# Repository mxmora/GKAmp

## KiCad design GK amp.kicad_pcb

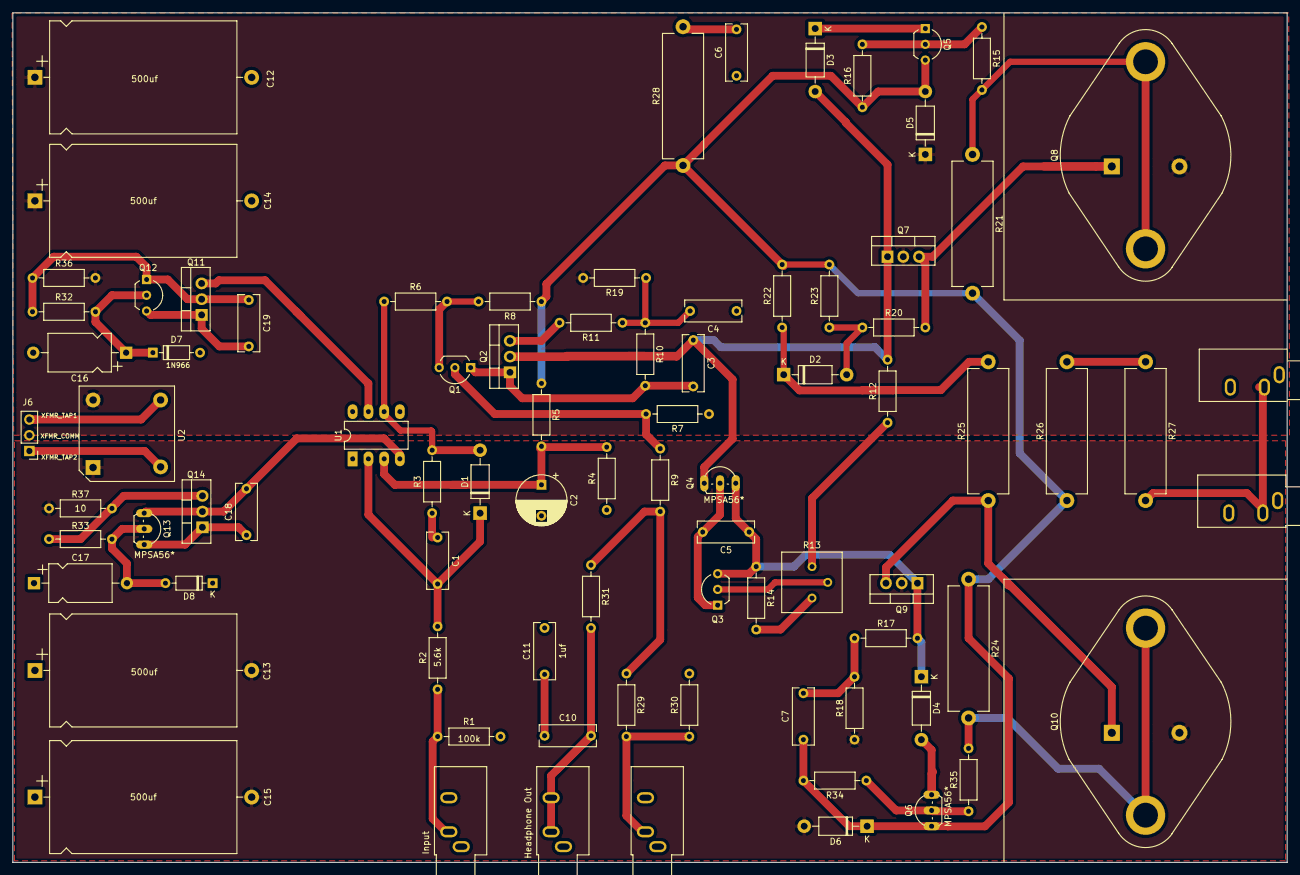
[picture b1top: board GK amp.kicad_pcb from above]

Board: 2 copper layers, 205.7 x 137.2 mm, 84 parts (0 on the bottom side), 48 nets.

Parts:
C1, C6: .1uf; C_Rect_L9.0mm_W3.3mm_P7.50mm_MKT
C2: 10uf; CP_Radial_D8.0mm_P5.00mm
C3: 100pF; C_Rect_L9.0mm_W3.3mm_P7.50mm_MKT
C4: 500; C_Rect_L9.0mm_W3.3mm_P7.50mm_MKT
C5: .01uf; C_Rect_L9.0mm_W3.3mm_P7.50mm_MKT
C7: 220uf; C_Rect_L9.0mm_W3.3mm_P7.50mm_MKT
C10, C11: 1uf; C_Rect_L9.0mm_W3.3mm_P7.50mm_MKT
C12, C13, C14, C15: 500uf; CP_Axial_L30.0mm_D18.0mm_P35.00mm_Horizontal
C16, C17: 10uf; CP_Axial_L10.0mm_D6.0mm_P15.00mm_Horizontal
C18, C19: 500pF; C_Rect_L9.0mm_W3.3mm_P7.50mm_MKT
D1, D2, D3, D4, D5, D6: 1N4002; D_DO-41_SOD81_P10.16mm_Horizontal
D7, D8: Zen; D_DO-35_SOD27_P7.62mm_Horizontal
J1, J2: SPEAKER; Jack_3.5mm_CUI_SJ1-3533NG_Horizontal
J3: Direct Out; Jack_3.5mm_CUI_SJ1-3533NG_Horizontal
J4: AudioJack3; Jack_3.5mm_CUI_SJ1-3533NG_Horizontal
J5: IN; Jack_3.5mm_CUI_SJ1-3533NG_Horizontal
J6: Conn_01x03_Male; PinHeader_1x03_P2.54mm_Vertical
Q1, Q3, Q5, Q12: MPSA06; TO-92_Inline_Wide
Q2, Q9: MJE15031; TO-220-3_Vertical
Q4, Q6, Q13: MPSA56*; TO92-CBE
Q7: MJE15030; TO-220-3_Vertical
Q8: MJ-15001; TO-3
Q10: MJ-15002; TO-3
Q11, Q14: TIP31; TO-220-3_Vertical
R1, R3: 100k; R_Axial_DIN0207_L6.3mm_D2.5mm_P10.16mm_Horizontal
R2: 5.6k; R_Axial_DIN0207_L6.3mm_D2.5mm_P10.16mm_Horizontal
R4, R29: 12k; R_Axial_DIN0207_L6.3mm_D2.5mm_P10.16mm_Horizontal
R5, R32, R33: 56k; R_Axial_DIN0207_L6.3mm_D2.5mm_P10.16mm_Horizontal
R6, R8: 3.74k; R_Axial_DIN0207_L6.3mm_D2.5mm_P10.16mm_Horizontal
R7: 4.75k; R_Axial_DIN0207_L6.3mm_D2.5mm_P10.16mm_Horizontal
R9: 4.99k; R_Axial_DIN0207_L6.3mm_D2.5mm_P10.16mm_Horizontal
R10, R14, R15: 1k; R_Axial_DIN0207_L6.3mm_D2.5mm_P10.16mm_Horizontal
R11: 100; R_Axial_DIN0207_L6.3mm_D2.5mm_P10.16mm_Horizontal
R12: 3.3k; R_Axial_DIN0207_L6.3mm_D2.5mm_P10.16mm_Horizontal
R13: 1k; Potentiometer_Bourns_3386P_Vertical
R16, R22, R23, R30, R34: 470; R_Axial_DIN0207_L6.3mm_D2.5mm_P10.16mm_Horizontal
R17, R18, R31: 2.7k 1W; R_Axial_DIN0207_L6.3mm_D2.5mm_P10.16mm_Horizontal
R19, R20: 22; R_Axial_DIN0207_L6.3mm_D2.5mm_P10.16mm_Horizontal
R21, R24, R26, R27: .33 5W; R_Axial_Power_L20.0mm_W6.4mm_P22.40mm
R25: 22; R_Axial_Power_L20.0mm_W6.4mm_P22.40mm
R28: 5 5w; R_Axial_Power_L20.0mm_W6.4mm_P22.40mm
R35: 1K; R_Axial_DIN0207_L6.3mm_D2.5mm_P10.16mm_Horizontal
R36, R37: 10; R_Axial_DIN0207_L6.3mm_D2.5mm_P10.16mm_Horizontal
U1: LF351N; DIP-8_W7.62mm_LongPads
U2: Bridge; Diode_Bridge_15.1x15.1x6.3mm_P10.9mm

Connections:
A: C12.1, C14.1, D5.1, Q7.2, Q8.2, R19.2, R36.2, U2.4
B: Q11.3, U1.7
C: C18.2, Q13.E, Q14.2, U1.4
D: C13.2, C15.2, D6.2, Q9.2, Q10.2, R18.1, R37.2, U2.1
GND: C2.2, C4.1, C6.1, C11.2, C12.2, C13.1, C14.2, C15.1, C16.2, C17.1, D7.2, D8.1, J1.S, J2.S, J3.S, J4.S, J5.S, J6.2, R1.1, R4.1, R7.1, R30.2
unnamed: C1.1, R3.1
unnamed: C1.2, D1.1, R2.2, U1.2
unnamed: C2.1, R4.2, R5.2, U1.3
unnamed: C3.1, D3.2, Q2.2, Q4.E, Q7.1, R12.2
unnamed: C3.2, Q1.1, Q2.1, R10.2
unnamed: C4.2, R10.1, R11.1, R19.1
unnamed: C5.1, D4.1, Q3.3, Q4.C, Q9.1, R14.1, R17.2
unnamed: C5.2, Q3.1, Q4.B
unnamed: C6.2, R28.2
unnamed: C7.1, D5.2, D6.1, Q5.3, Q6.E, R5.1, R8.1, R16.1, R21.2, R22.2, R23.2, R24.1, R26.1, R28.1, R34.2
unnamed: C7.2, R17.1, R18.2
unnamed: C10.1, C11.1
unnamed: C10.2, J4.R, J4.T, R31.2
unnamed: C16.1, D7.1, Q12.2, R32.2
unnamed: C17.2, D8.2, Q13.B, R33.1
unnamed: C18.1, Q13.C, Q14.1
unnamed: C19.1, Q11.2, Q12.1, R32.1, R36.1
unnamed: C19.2, Q11.1, Q12.3
unnamed: D1.2, R3.2, R6.1, U1.6
unnamed: D2.1, R22.1, R25.2
unnamed: D2.2, R20.1, R23.1
unnamed: D3.1, Q5.1
unnamed: D4.2, Q6.C
unnamed: J1.T, J2.T, R27.2
unnamed: J3.T, R29.2, R30.1
unnamed: J5.T, R1.2, R2.1
unnamed: J6.1, U2.2
unnamed: J6.3, U2.3
unnamed: Q1.2, R7.2, R9.1
unnamed: Q1.3, R6.2, R8.2
unnamed: Q2.3, R11.2
unnamed: Q3.2, R13.2
unnamed: Q5.2, R15.1, R16.2
unnamed: Q6.B, R34.1, R35.1
unnamed: Q7.3, Q8.1, R20.2
unnamed: Q8.3, R15.2, R21.1
unnamed: Q9.3, Q10.1, R25.1
unnamed: Q10.3, R24.2, R35.2
unnamed: Q14.3, R33.2, R37.1
unnamed: R12.1, R13.3
unnamed: R13.1, R14.2
unnamed: R26.2, R27.1
unnamed: R9.2, R29.1, R31.1

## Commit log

2019-05-17 Add files
2019-05-17 fix up parts linkage
2019-05-19 Fix up footprints and layout PCB
2019-05-20 rearange the board a little
2019-05-20 leave room for heatsink
2019-05-23 more layout changes
2019-05-25 fix power input
